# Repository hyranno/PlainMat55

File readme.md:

Simple 5*5 key matrix with connectors.

Handy for keyboard development.

Used KiCad plugins (install via PCM)
* com.github.adamws.kicad-kbplacer
* com.github.perigoso.keyswitch-kicad-library

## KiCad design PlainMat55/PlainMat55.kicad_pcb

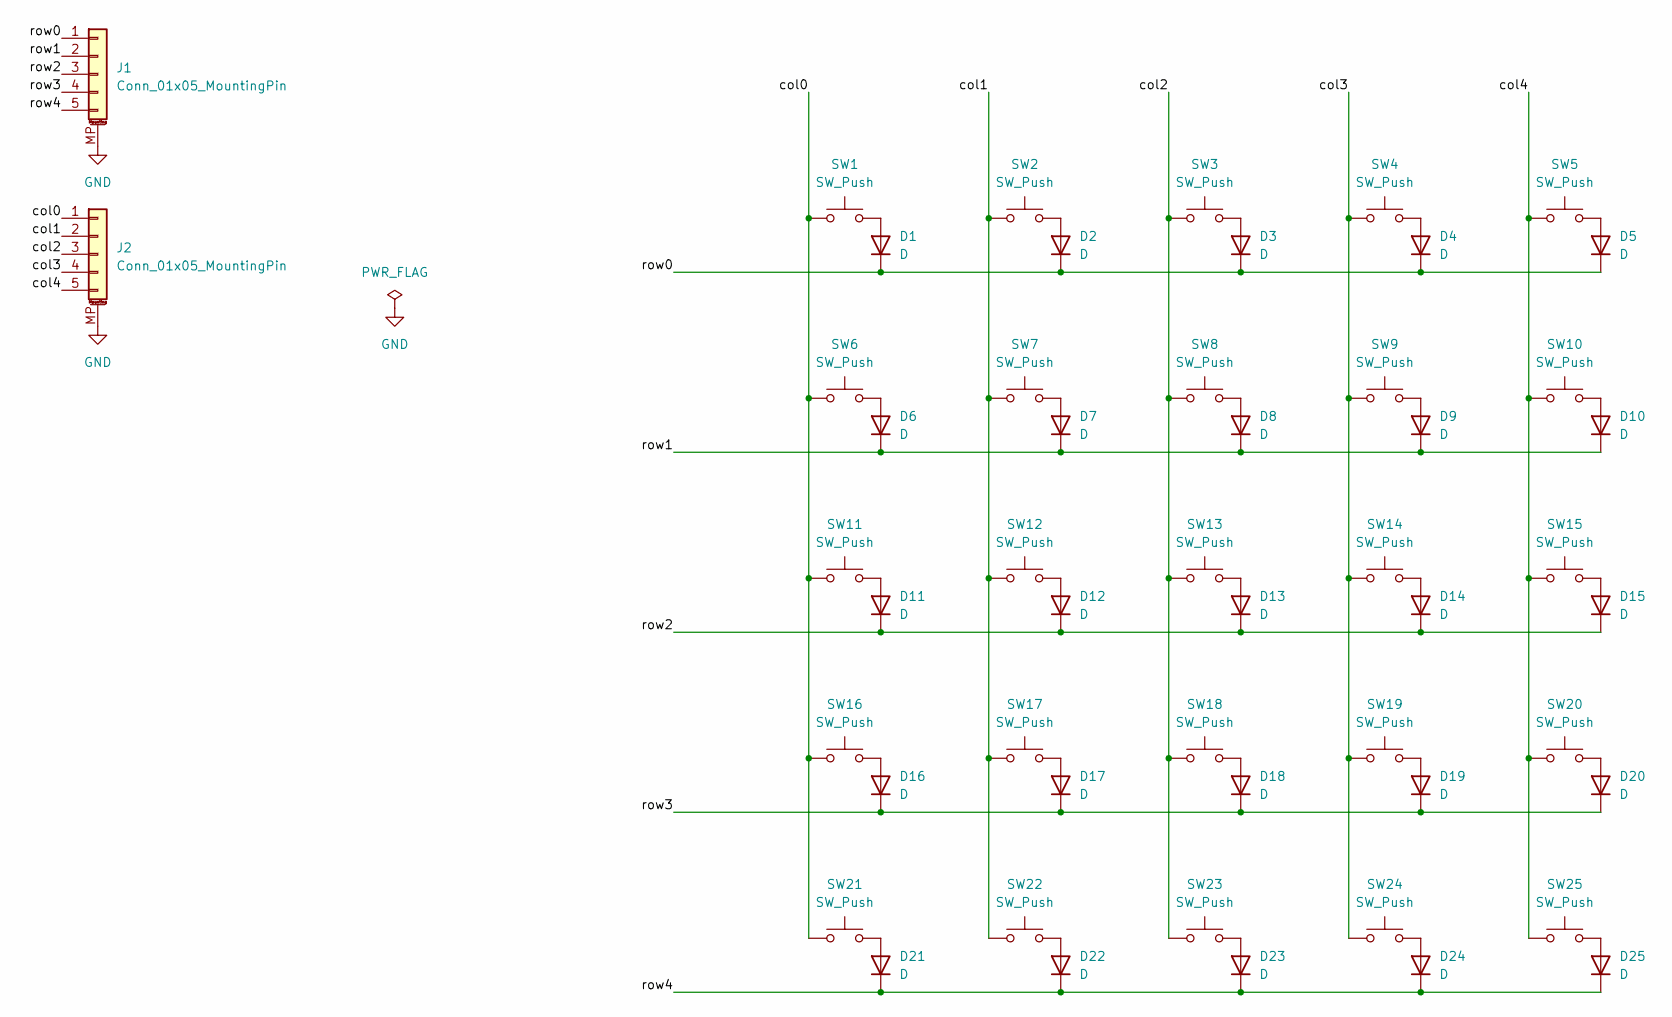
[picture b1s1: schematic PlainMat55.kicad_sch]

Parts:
D1, D2, D3, D4, D5, D6, D7, D8, D9, D10, D11, D12, D13, D14, D15, D16, D17, D18, D19, D20, D21, D22, D23, D24, D25: D; D_0402_1005Metric; Manufacturer Part number 1N4148WL2-TP
J1, J2: Conn_01x05_MountingPin; JST_PH_S5B-PH-SM4-TB_1x05-1MP_P2.00mm_Horizontal; Manufacturer Part number S5B-PH-SM4-TB
SW1, SW2, SW3, SW4, SW5, SW6, SW7, SW8, SW9, SW10, SW11, SW12, SW13, SW14, SW15, SW16, SW17, SW18, SW19, SW20, SW21, SW22, SW23, SW24, SW25: SW_Push; SW_Hotswap_Kailh_Choc_V1V2; Manufacturer Part number 5118

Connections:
/col0: J2.1, SW1.1, SW6.1, SW11.1, SW16.1, SW21.1
/col1: J2.2, SW2.1, SW7.1, SW12.1, SW17.1, SW22.1
/col2: J2.3, SW3.1, SW8.1, SW13.1, SW18.1, SW23.1
/col3: J2.4, SW4.1, SW9.1, SW14.1, SW19.1, SW24.1
/col4: J2.5, SW5.1, SW10.1, SW15.1, SW20.1, SW25.1
/row0: D1.1 (K), D2.1 (K), D3.1 (K), D4.1 (K), D5.1 (K), J1.1
/row1: D6.1 (K), D7.1 (K), D8.1 (K), D9.1 (K), D10.1 (K), J1.2
/row2: D11.1 (K), D12.1 (K), D13.1 (K), D14.1 (K), D15.1 (K), J1.3
/row3: D16.1 (K), D17.1 (K), D18.1 (K), D19.1 (K), D20.1 (K), J1.4
/row4: D21.1 (K), D22.1 (K), D23.1 (K), D24.1 (K), D25.1 (K), J1.5
GND: J1.MP (MountPin), J2.MP (MountPin)
unnamed: D1.2 (A), SW1.2
unnamed: D2.2 (A), SW2.2
unnamed: D3.2 (A), SW3.2
unnamed: D4.2 (A), SW4.2
unnamed: D5.2 (A), SW5.2
unnamed: D6.2 (A), SW6.2
unnamed: D7.2 (A), SW7.2
unnamed: D8.2 (A), SW8.2
unnamed: D9.2 (A), SW9.2
unnamed: D10.2 (A), SW10.2
unnamed: D11.2 (A), SW11.2
unnamed: D12.2 (A), SW12.2
unnamed: D13.2 (A), SW13.2
unnamed: D14.2 (A), SW14.2
unnamed: D15.2 (A), SW15.2
unnamed: D16.2 (A), SW16.2
unnamed: D17.2 (A), SW17.2
unnamed: D18.2 (A), SW18.2
unnamed: D19.2 (A), SW19.2
unnamed: D20.2 (A), SW20.2
unnamed: D21.2 (A), SW21.2
unnamed: D22.2 (A), SW22.2
unnamed: D23.2 (A), SW23.2
unnamed: D24.2 (A), SW24.2
unnamed: D25.2 (A), SW25.2

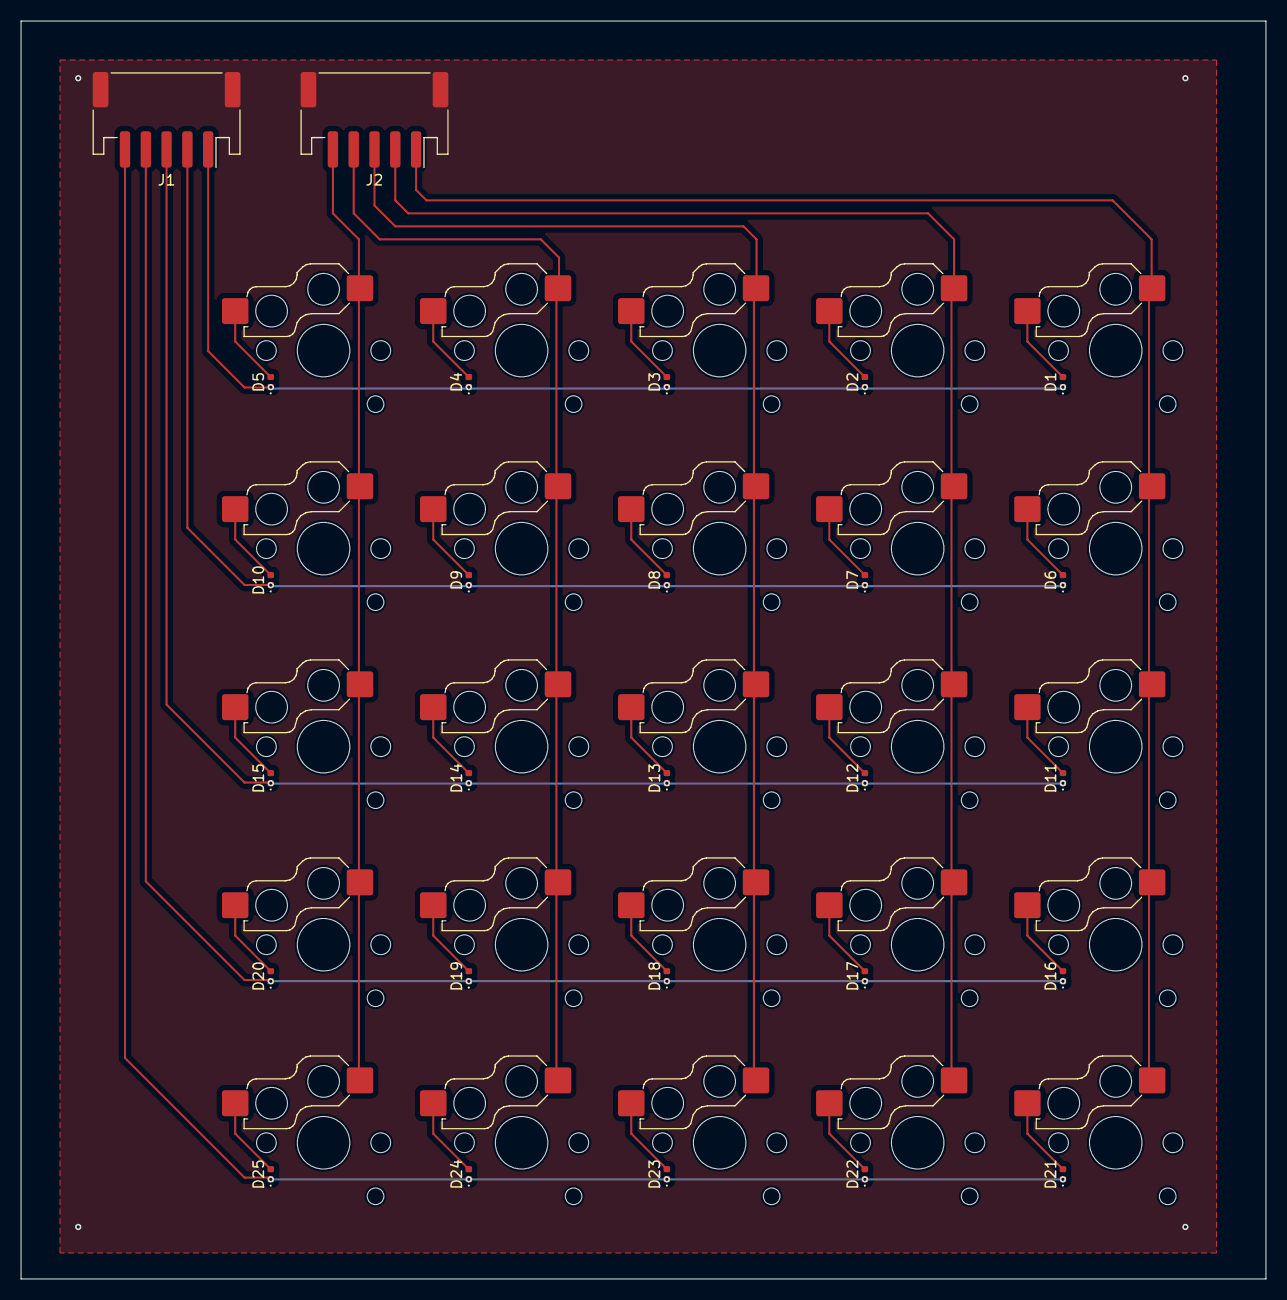
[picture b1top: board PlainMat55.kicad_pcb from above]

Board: 2 copper layers, 119.8 x 121.0 mm, 52 parts (25 on the bottom side), 36 nets.

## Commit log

2025-05-07 init
2025-05-07 add layout
2025-05-08 update bom
2025-05-08 add pcb
2025-05-09 add fab script for elecrow
2025-05-13 fix fabscript
